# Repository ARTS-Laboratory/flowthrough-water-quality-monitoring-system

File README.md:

# Flowthrough Water Quality Monitoring System

This system monitors water quality by measuring conductivity, pH, and temperature, ensuring continuous operation with minimal maintenance. Moreover, versions of this system enable the use of time-domain nuclear magnetic resonance to be performed in situ. It features a robust construction that protects electrical components from environmental damage, supports an adequate flow rate for in situ water sampling, and enables data transmission to a server for analysis.

<p align="center">
Figure 1: flow-through water quality monitoring deployed at USC to monitor water quality in the Rocky Branch in Columbia South Carolina.
</p>

## System Development
Contains the hardware and software developed for the project. 

## Licensing and Citation

This work is licensed under a Creative Commons Attribution-ShareAlike 4.0 International License [cc-by-sa 4.0].

Cite this as: 

@Misc{ARTSLabFlowthroughWaterQuality,    
  author = {ARTS-Lab},  
  howpublished = {GitHub},  
  title  = {Flowthrough Water Quality Monitoring System},   
  groups = {ARTS-Lab},    
  url    = {https://github.com/ARTS-Laboratory/flowthrough-water-quality-monitoring-system},   
}

<p align="center">
QR code for repo.
</p>

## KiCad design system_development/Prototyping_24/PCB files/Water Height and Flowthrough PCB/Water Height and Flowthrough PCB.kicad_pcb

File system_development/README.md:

# System Development
Variations of the flow through the water quality system are being developed. Named after lakes in South Carolina 

## Keowee
A flow-through water quality monitoring system that measures PH, TDS, water temperature, and ambient temperature.

## Moultrie
A flow-through water quality monitoring system that integrates nuclear magnetic resonance monitoring and measures PH, TDS, water temperature, and ambient temperature.

## Marion
A prototype project beginning work in May of 2024 to combine a flowthrough NMR, a water quality, and a water height monitoring system.

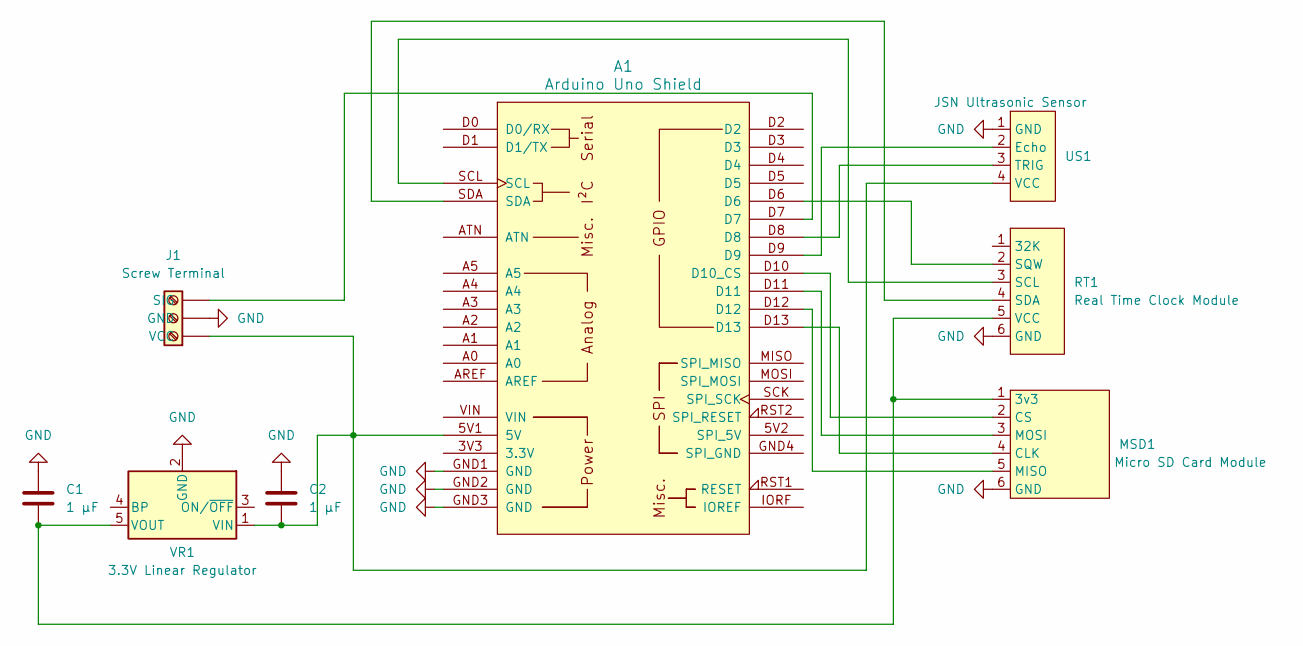
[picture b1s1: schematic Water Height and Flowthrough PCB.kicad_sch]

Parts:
A1: Arduino Uno Shield; Arduino_101_Shield
C1, C2: 1 μF; C_1206_3216Metric
J1: Screw Terminal; TerminalBlock_Phoenix_MKDS-1,5-3-5.08_1x03_P5.08mm_Horizont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
MSD1: Micro SD Card Module; PinSocket_1x06_P2.54mm_Vertical
RT1: Real Time Clock Module; PinSocket_1x06_P2.54mm_Vertical
US1: JSN Ultrasonic Sensor; PinSocket_1x04_P2.54mm_Vertical
VR1: 3.3V Linear Regulator; SOT-23-5

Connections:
GND: A1.GND1 (GND), A1.GND2 (GND), A1.GND3 (GND), C1.1, C2.1, J1.2 (GND), MSD1.6 (GND), RT1.6 (GND), US1.1 (GND), VR1.2 (GND)
unnamed: A1.5V1 (5V), C2.2, J1.1 (VCC), US1.4 (VCC), VR1.1 (VIN)
unnamed: A1.D10 (D10_CS), MSD1.2 (CS)
unnamed: A1.D7, J1.3 (SIG)
unnamed: C1.2, MSD1.1 (3v3), RT1.5 (VCC), VR1.5 (VOUT)
unnamed: A1.D13, MSD1.4 (CLK)
unnamed: A1.D12, MSD1.5 (MISO)
unnamed: A1.D11, MSD1.3 (MOSI)
unnamed: A1.SCL, RT1.3 (SCL)
unnamed: A1.SDA, RT1.4 (SDA)
unnamed: A1.D6, RT1.2 (SQW)
unnamed: A1.D9, US1.2 (Echo)
unnamed: A1.D8, US1.3 (TRIG)

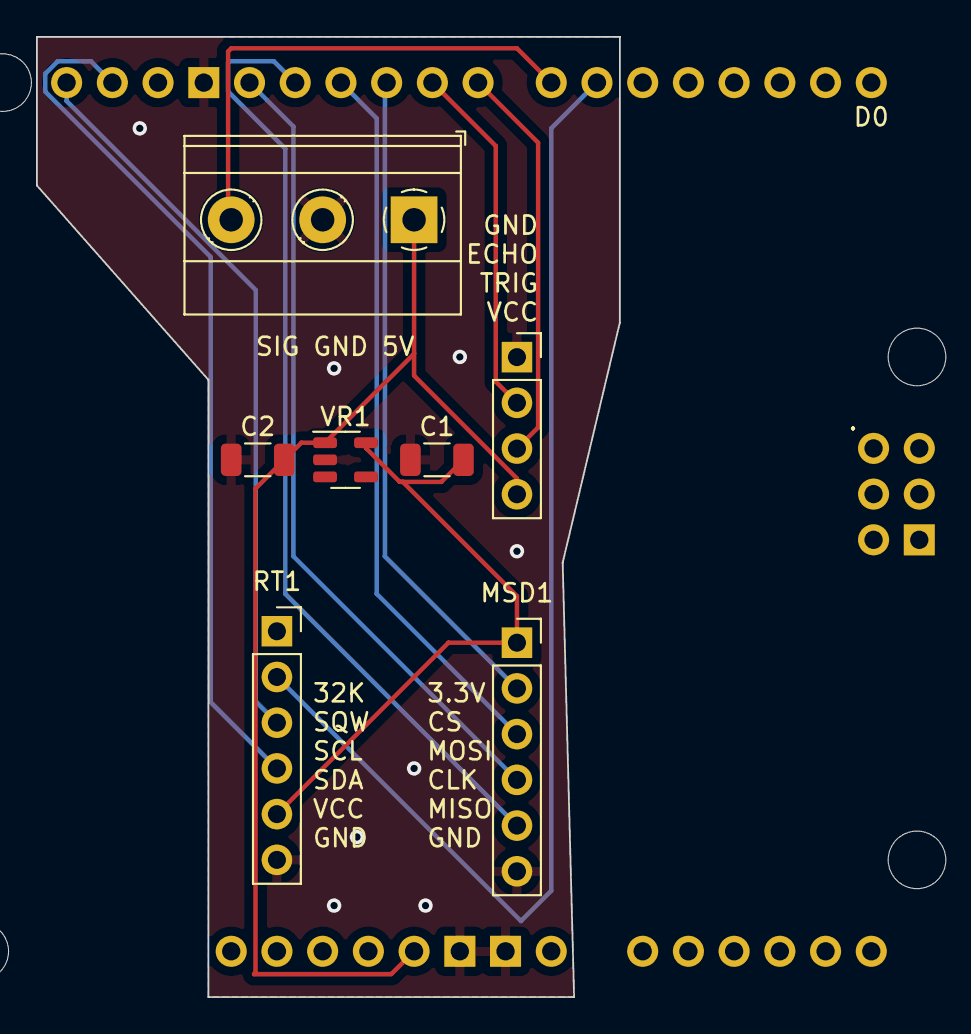
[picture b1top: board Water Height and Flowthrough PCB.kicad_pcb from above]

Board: 2 copper layers, 32.4 x 53.3 mm, 8 parts (0 on the bottom side), 13 nets.

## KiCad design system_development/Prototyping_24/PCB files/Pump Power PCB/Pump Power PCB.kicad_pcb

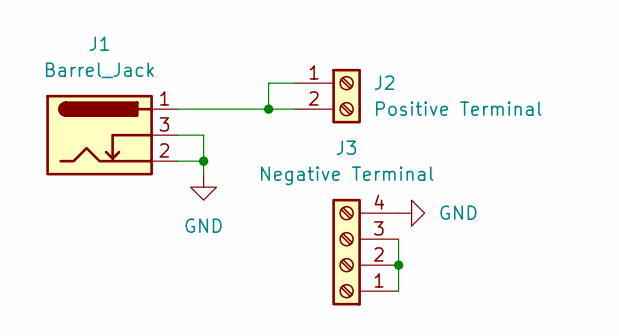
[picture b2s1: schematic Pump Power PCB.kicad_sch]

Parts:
J1: Barrel_Jack; BarrelJack_Horizontal
J2: Positive Terminal; TerminalBlock_Phoenix_MKDS-1,5-2-5.08_1x02_P5.08mm_Horizont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
J3: Negative Terminal; TerminalBlock_Phoenix_MKDS-1,5-4-5.08_1x04_P5.08mm_Horizont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

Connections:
GND: J1.2, J1.3, J3.4
unnamed: J1.1, J2.1, J2.2
unnamed: J3.1, J3.2, J3.3

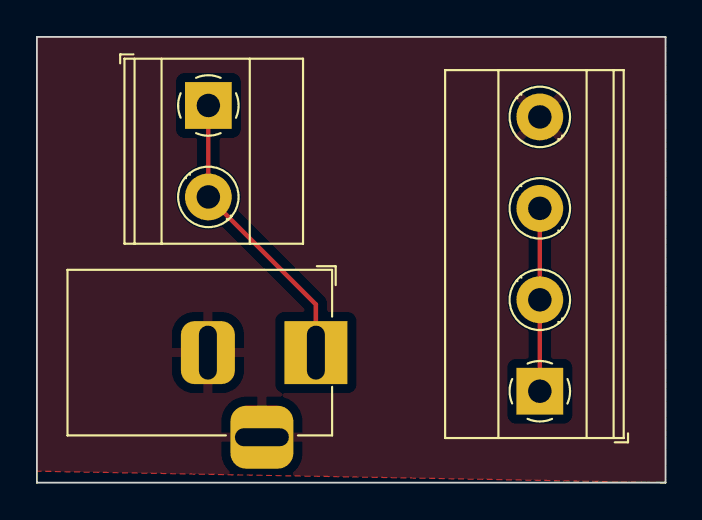
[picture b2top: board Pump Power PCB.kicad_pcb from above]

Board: 2 copper layers, 34.9 x 24.8 mm, 3 parts (0 on the bottom side), 3 nets.

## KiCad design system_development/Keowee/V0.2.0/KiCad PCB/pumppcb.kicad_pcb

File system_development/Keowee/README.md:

# Keowee
A flow-through water quality monitoring system that measures PH, TDS, Water Temperature, and ambient Temperature.

## V0.1
1. An initial senior design project undertaken at USC that laid out initial system aspects. 

## V0.2
1. Measures PH, TDS, Water Temperature, and ambient Temperature.
2. Saves the Data collected on an SD card.
3. Using RTC to control and display the sampling time.
4. Using a relay to control the pumps.

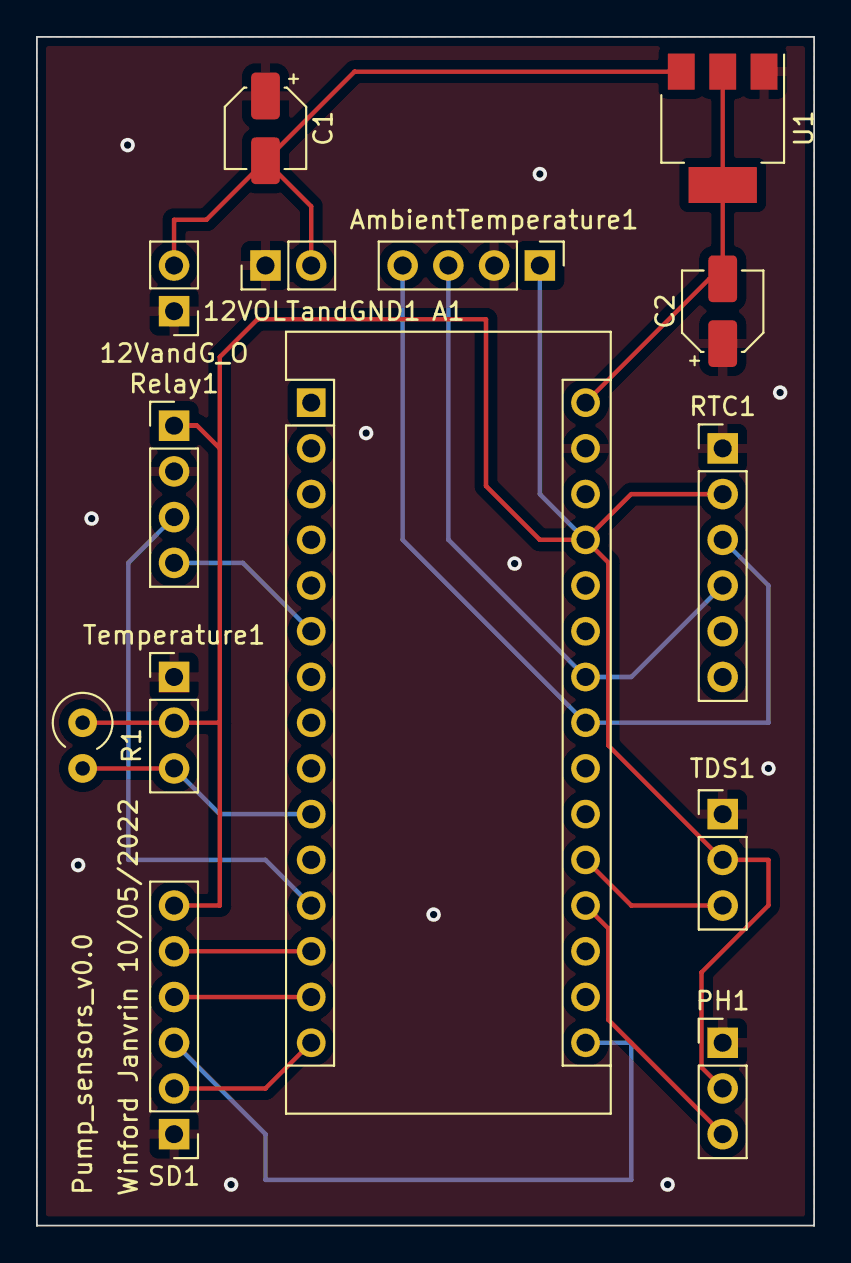
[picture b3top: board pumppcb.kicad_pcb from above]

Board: 2 copper layers, 43.2 x 66.0 mm, 14 parts (0 on the bottom side), 15 nets.

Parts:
12VOLTandGND1, 12VandG_O: Conn_01x02; PinHeader_1x02_P2.54mm_Vertical
A1: Arduino_Nano_v3.x; Arduino_Nano
AmbientTemperature1: Conn_01x04; PinHeader_1x04_P2.54mm_Vertical
C1, C2: C; CP_Elec_4x5.8
PH1: Conn_01x03; PinHeader_1x03_P2.54mm_Vertical
R1: R_Small_US; R_Axial_DIN0309_L9.0mm_D3.2mm_P2.54mm_Vertical
RTC1: Conn_01x06; PinHeader_1x06_P2.54mm_Vertical
Relay1: Conn_01x04; PinHeader_1x04_P2.54mm_Vertical
SD1: Conn_01x06; PinHeader_1x06_P2.54mm_Vertical
TDS1: Conn_01x03; PinHeader_1x03_P2.54mm_Vertical
Temperature1: Conn_01x03; PinHeader_1x03_P2.54mm_Vertical
U1: AMS1117-5.0; SOT-223-3_TabPin2

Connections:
/12v: 12VOLTandGND1.2, 12VandG_O.2, C1.2, U1.3 (VI)
/A0: A1.19 (A0), PH1.3
/A1: A1.20 (A1), TDS1.3
/CLK: A1.16 (D13), SD1.3
/CS: A1.13 (D10), SD1.5
/D7: A1.10 (D7), R1.2, Temperature1.3
/IN1: A1.12 (D9), Relay1.3
/IN2: A1.6 (D3), Relay1.4
/MISO: A1.15 (D12), SD1.2
/MOSI: A1.14 (D11), SD1.4
/SCL: A1.24 (A5), AmbientTemperature1.3, RTC1.4
/SDA: A1.23 (A4), AmbientTemperature1.4, RTC1.3
/VIN: A1.30 (VIN), C2.2, U1.2 (VO)
GND: 12VOLTandGND1.1, 12VandG_O.1, A1.29 (GND), AmbientTemperature1.2, C1.1, C2.1, PH1.1, RTC1.1, Relay1.2, SD1.1, TDS1.1, Temperature1.1, U1.1 (GND)
VCC: A1.27 (+5V), AmbientTemperature1.1, PH1.2, R1.1, RTC1.2, Relay1.1, SD1.6, TDS1.2, Temperature1.2

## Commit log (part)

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2022-09-15 Flow through water quality system Arduino code
2022-10-03 Create Pumpsystemcodeoctober.ino
    Same as 0.1 except pump runs for 60 seconds takes measurements then turns off for 5 minutes.
2024-05-12 initial push of re-vamped repo
2024-05-12 Added front page readme
2024-05-12 added Moultrie v0.1
2024-05-16 Created PCB's for Water Height Monitoring
2024-05-16 Altered PCB's
2024-05-16 Added Parts List
2024-05-30 Added Code
2024-06-14 Renamed Prototype to Marion
2024-06-14 Updated Rough CAD
    for now this mostly serves to make sure we have the dimensions right before we build. It'll look nicer later
2024-07-18 added markdown file for documentation
2024-07-18 fix relay image
2024-07-18 fix md
2024-07-18 merged text onto markdown file
2024-07-23 hydroponics testing kit with sd card module image
2024-07-23 Rename Labeled Hydroponics Testing Kit.png to labeled_hydroponics_testing_kit
2024-07-23 Labeled Hydroponics Testing Kit with SD Card Reader
2024-07-23 Updated sensor array
2024-07-23 Current Code for the sensor array and pump
2024-07-23 Create temp
2024-07-23 current code for the testing kit
2024-07-23 Adding libraries
2024-11-23 added qr code
2025-01-21 Create Flowthrough_NMR_labVIEW
2025-03-24 added solar panel prints
2025-05-27 moved in v0.3 from Dan's SPIE work
2025-09-22 added v 0.2.1
2025-09-26 added cart folder
2025-10-14 Update BOM-v0.3-cart.xlsx
    Added all supplies to BOM
2026-06-03 New CAD files added
2026-06-08 BOM updated
2026-06-08 Updated BOM
2026-06-15 Updates in BOM
